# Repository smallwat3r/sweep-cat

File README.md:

# Sweep Cat

A 30-key version of the fantastic [Sweep 2.2](https://github.com/davidphilipbarr/Sweep), featuring my cat, Lila.

## v2

This newer version adds some slight angle to the two outermost columns, which makes it more comfortable and natural to type on.

- Splay on pinkie finger: 8°
- Splay on ring finger: 3°

## v1

This is the original version of the Sweep Cat.

## Contents

This repository contains:
- Gerber files (comptatible with [JLCPCB](https://jlcpcb.com))
- Kicad files

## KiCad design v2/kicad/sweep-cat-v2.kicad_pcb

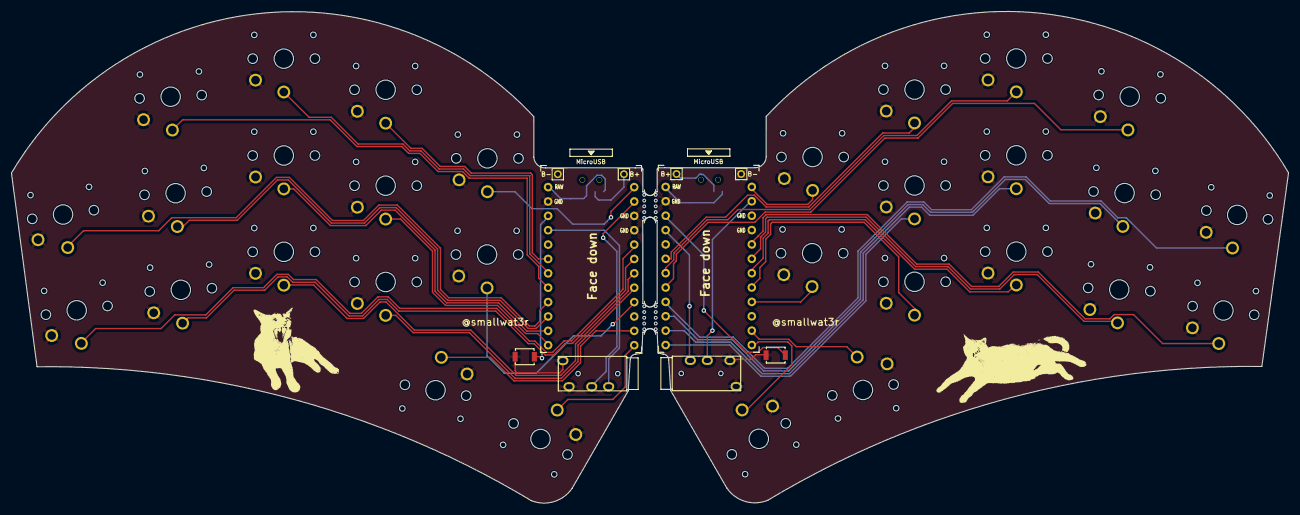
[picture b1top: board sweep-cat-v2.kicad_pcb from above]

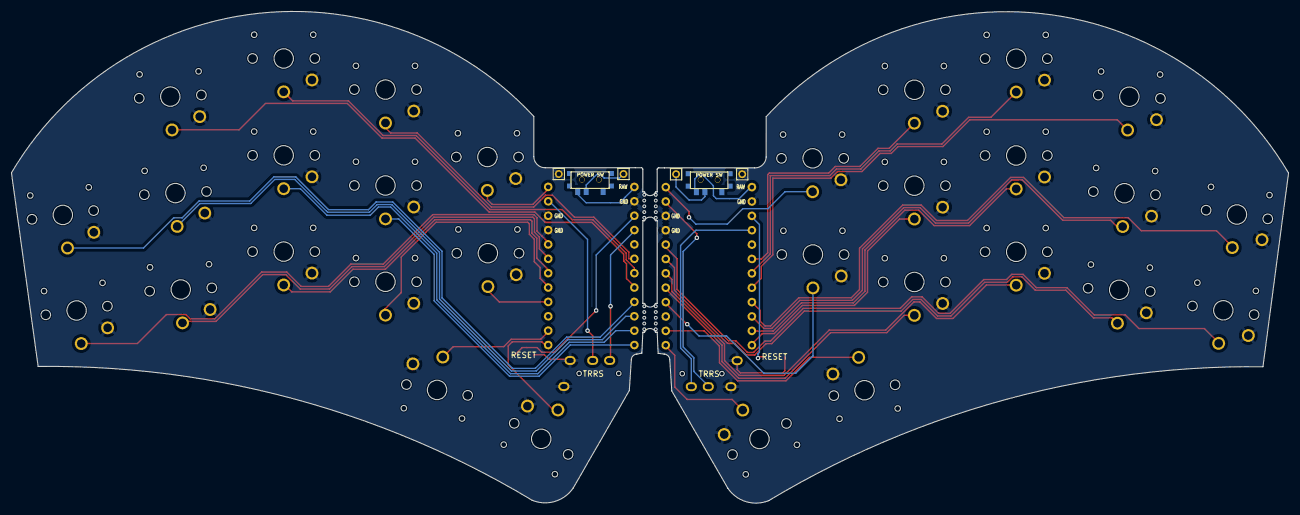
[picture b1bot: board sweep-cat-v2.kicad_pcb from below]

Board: 2 copper layers, 225.7 x 86.9 mm, 44 parts (2 on the bottom side), 39 nets.

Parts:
B+: MountingHole_Pad; 1pin_conn
B+#2: MountingHole_Pad; 1pin_conn
B-: MountingHole_Pad; 1pin_conn
B-#2: MountingHole_Pad; 1pin_conn
J1, J2: AudioJack4dpb; TRRS-PJ-320A
POWER SW: SW_SPDT; SPDT_C128955
POWER SW#2: SW_SPDT; SPDT_C128955
RSW1, RSW2: SW_Push; SW_SPST_B3U-1000P
SW3, SW3_r1, SW4, SW4_r1, SW5, SW5_r1, SW7_r1, SW8, SW8_r1, SW9, SW9_r1, SW10, SW11, SW11_r1, SW12, SW12_r1, SW13_r1, SW14, SW15, SW15_r1, SW16, SW16_r1, SW17, SW17_r1, SW18, SW18_r1, SW20, SW20_r1, SW21, SW21_r1: SW_Push; choc-v1-with-millmax
U1, U2: ProMicro-kbd; ProMicro_v3_min
mouse-bite-2mm-slot, mouse-bite-2mm-slot#2: VAL**; mouse-bite-5mm-slot-with-space-for-track

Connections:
BT+: B+#2.1, POWER SW#2.2
BT+_r: B+.1, POWER SW.2
Switch2: SW3.1, U1.17
Switch2_r: SW3_r1.1, U2.17
Switch3: SW4.1, U1.18
Switch3_r: SW4_r1.1, U2.18
Switch4: SW5.1, U1.19
Switch4_r: SW5_r1.1, U2.19
Switch6: SW8.1, U1.16
Switch6_r: SW7_r1.1, U2.16
Switch7: SW9.1, U1.15
Switch7_r: SW8_r1.1, U2.15
Switch8: SW10.1, U1.14
Switch8_r: SW9_r1.1, U2.14
Switch9: SW11.1, U1.13
Switch9_r: SW11_r1.1, U2.13
Switch10: SW12.1, U1.1
Switch10_r: SW12_r1.1, U2.1
Switch11: SW14.1, U1.5
Switch11_r: SW13_r1.1, U2.5
Switch12: SW15.1, U1.6
Switch12_r: SW18_r1.1, U2.6
Switch13: SW16.1, U1.7
Switch13_r: SW15_r1.1, U2.7
Switch14: SW17.1, U1.8
Switch14_r: SW16_r1.1, U2.8
Switch15: SW18.1, U1.9
Switch15_r: SW17_r1.1, U2.9
Switch16: SW21.1, U1.11
Switch16_r: SW21_r1.1, U2.11
Switch17: SW20.1, U1.12
Switch17_r: SW20_r1.1, U2.12
Switch18: J2.R1, U1.2
Switch18_r: J1.R1, U2.2
gnd: B-.1, B-#2.1, J1.S, J1.T, J2.S, J2.T, RSW1.1, RSW2.1, SW3.2, SW3_r1.2, SW4.2, SW4_r1.2, SW5.2, SW5_r1.2, SW7_r1.2, SW8.2, SW8_r1.2, SW9.2, SW9_r1.2, SW10.2, SW11.2, SW11_r1.2, SW12.2, SW12_r1.2, SW13_r1.2, SW14.2, SW15.2, SW15_r1.2, SW16.2, SW16_r1.2, SW17.2, SW17_r1.2, SW18.2, SW18_r1.2, SW20.2, SW20_r1.2, SW21.2, SW21_r1.2, U1.3, U1.4, U1.23, U2.3, U2.4, U2.23
raw: POWER SW.3, POWER SW#2.3, U1.24, U2.24
reset: RSW1.2, U1.22
reset_r: RSW2.2, U2.22
vcc: J1.R2, J2.R2, U1.21, U2.21

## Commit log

2024-09-05 Add files
2024-09-05 Fix links
2024-09-05 Fix typo
2024-09-05 Add Gerber file
2024-09-05 Add keymap
2024-09-06 Update keymap
2024-09-06 Update layout
2024-09-09 Fix keymap
2024-09-09 Remove vial
2024-09-09 Add keymap as a submodule
2024-09-09 Rename submodule
2024-09-10 Remove subdmodule
2024-09-10 Use keymap from main
2024-10-01 Add version 2
2024-10-01 Add gerber files
2024-10-08 Fix typos
2024-10-08 Delete
2024-10-12 Rename files
2024-10-12 Rename project metadata
2024-10-17 Change keymap source
2024-10-18 Add splay values
2024-10-18 Edit README
2024-10-28 Remove keymap
